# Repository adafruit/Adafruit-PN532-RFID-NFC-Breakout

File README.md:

## Adafruit NFC/RFID controller breakout board - v1.6 PCB

<a href="http://www.adafruit.com/products/364"><br/>
Click here to purchase one from the Adafruit shop</a>

PCB files for the Adafruit NFC/RFID controller breakout board - v1.6. Format is EagleCAD schematic and board layout
* https://www.adafruit.com/product/364

### Description

The PN532 is the most popular NFC chip, and is what is embedded in pretty much every phone or device that does NFC. It can pretty much do it all, such as read and write to tags and cards, communicate with phones (say for payment processing), and 'act' like a NFC tag. If you want to do any sort of embedded NFC work, this is the chip you'll want to use!

NFC (Near Field Communications) is a way for two devices very close to each other to communicate. Sort of like a very short range bluetooth that doesn't require authentication. It is an extension of RFID, so anything you can do with RFID you can do with NFC. You can do more stuff with NFC as well, such as communicate bi-directionally with cell phones

Because it can read and write tags, you can always just use this for RFID-tag projects. We carry a few different tags that work great with this chip. It can also work with any other NFC/RFID Type 1 thru 4 tag.

The PN532 is also very flexible, you can use 3.3V TTL UART at any baud rate, I2C or SPI to communicate with it. This chip is also strongly supported by [libnfc](http://www.libnfc.org/), simply plug in an FTDI cable and use the FTDI serial port device to communicate - this lets you do NFC dev using any Linux/Mac/Windows computer! We also include onboard power LED, 3.3V regulator and an FTDI header so you can plug in an [FTDI friend](http://www.adafruit.com/products/284) or [FTDI cable](http://www.adafruit.com/products/70) and use with libnfc.

Comes with: the PN532 breakout board including a tuned 13.56MHz stripline antenna, 0.1" header, 2 jumpers/shunts and a 4050 level shifter chip. We also toss in a  13.56MHz 1K card! ([You can get more tags from us here](http://www.adafruit.com/category/55))

### License

Adafruit invests time and resources providing this open source design, please support Adafruit and open-source hardware by purchasing products from [Adafruit](https://www.adafruit.com)!

Designed by Limor Fried/Ladyada for Adafruit Industries.

Creative Commons Attribution/Share-Alike, all text above must be included in any redistribution. See license.txt for additional details.

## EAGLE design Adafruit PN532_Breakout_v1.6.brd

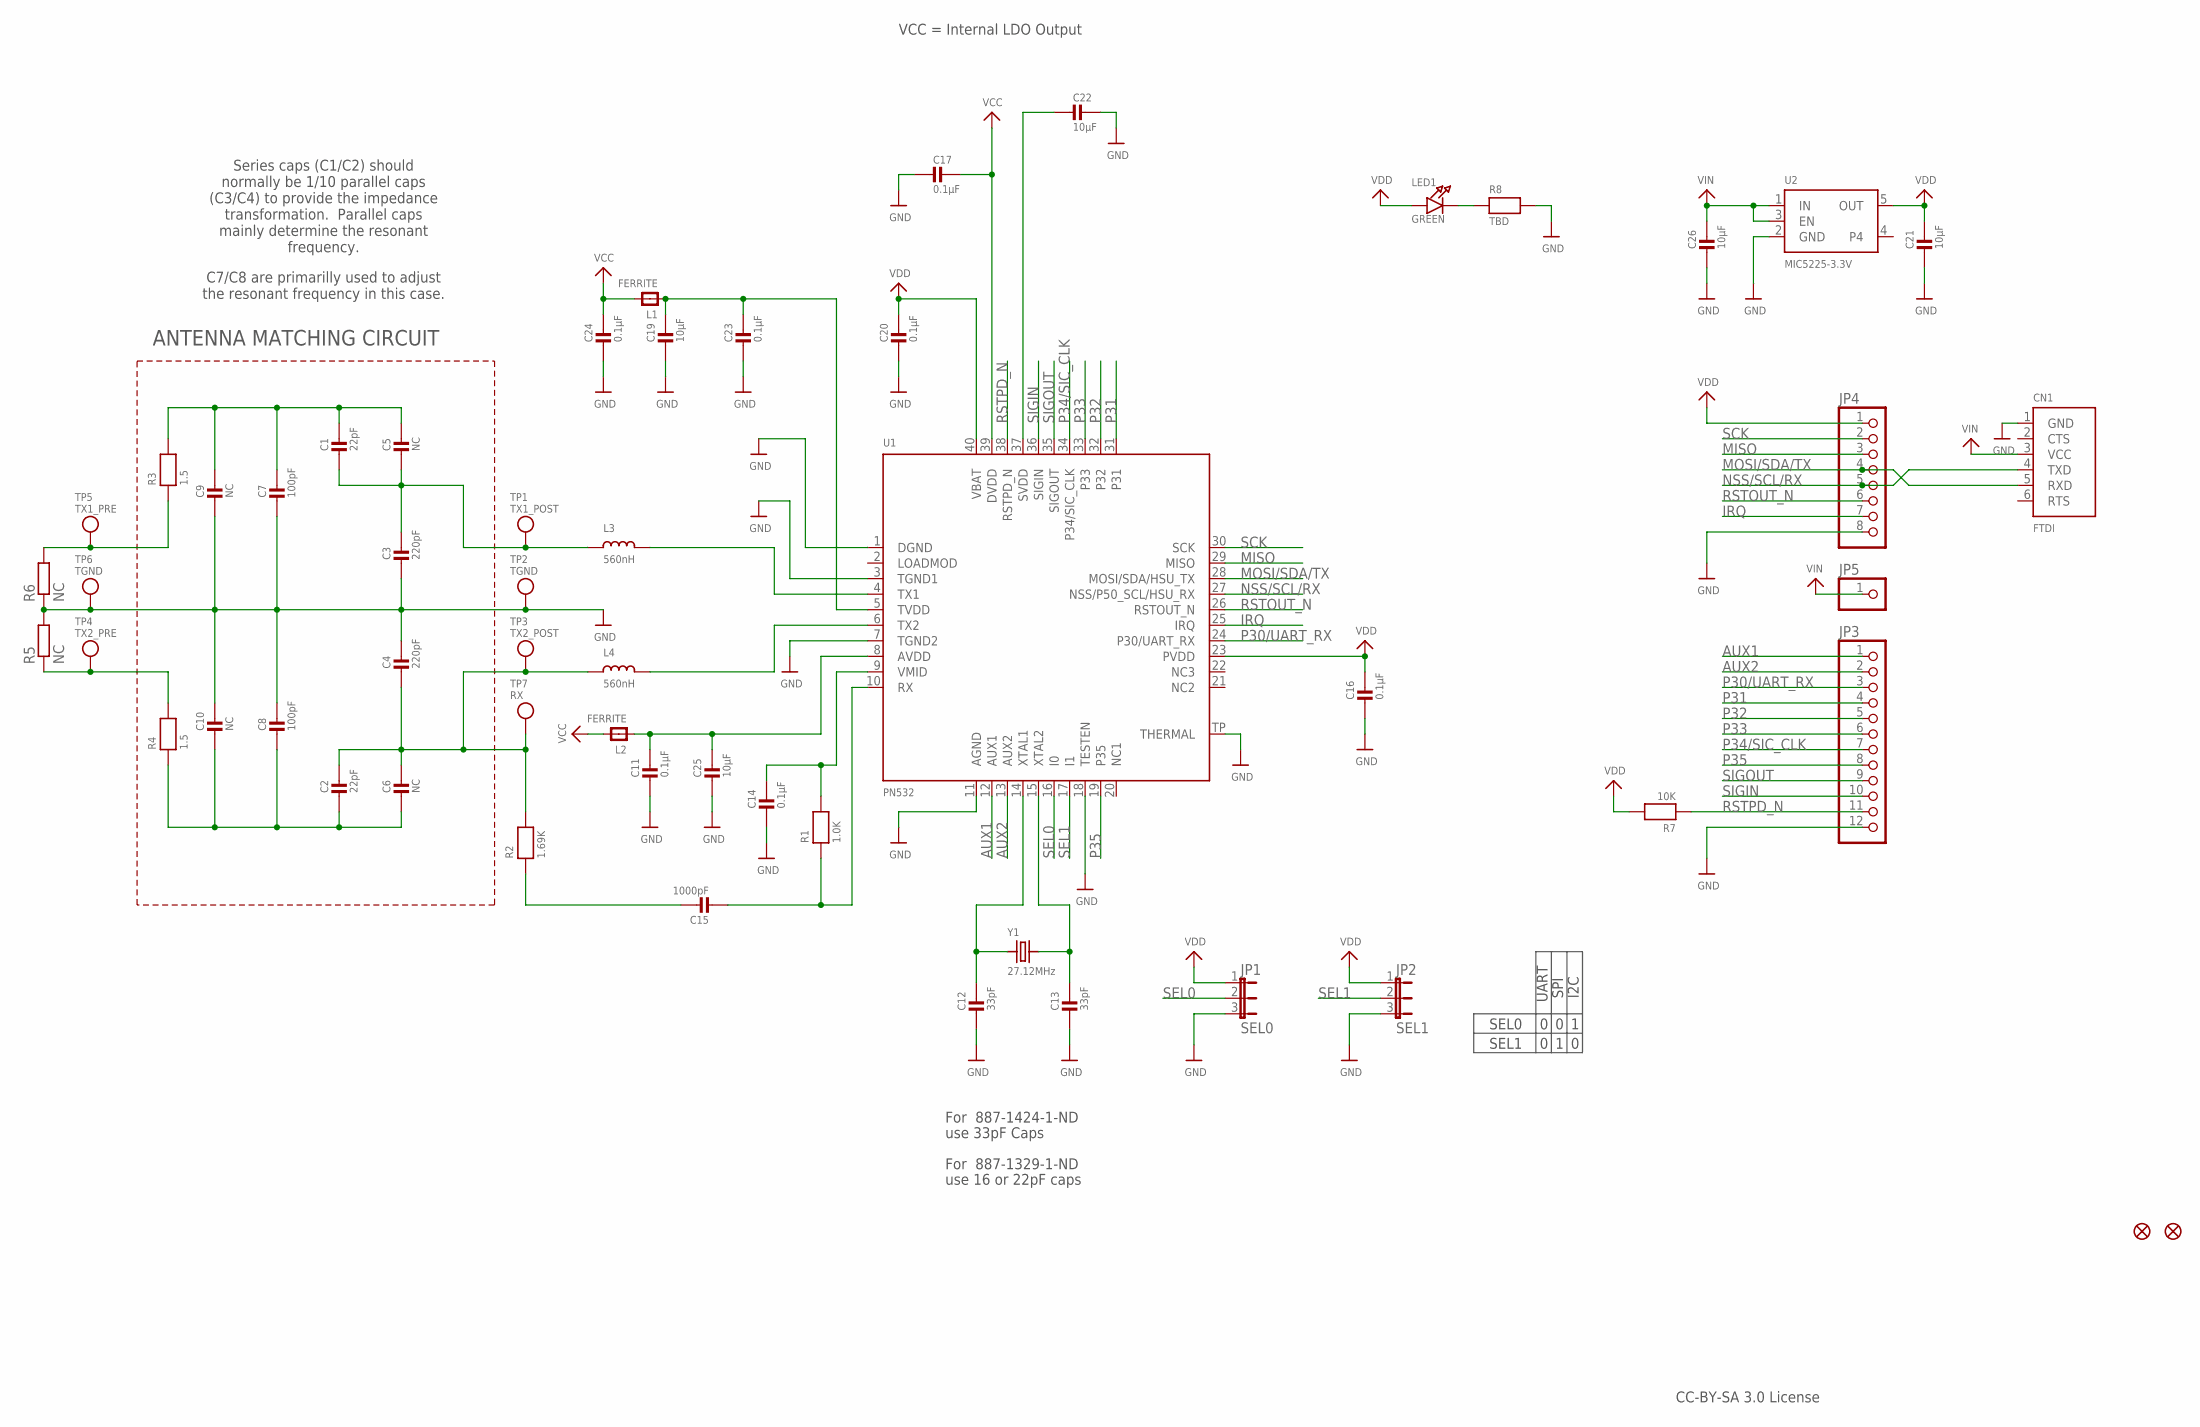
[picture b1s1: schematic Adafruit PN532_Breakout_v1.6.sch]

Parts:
C1, C2: 22pF; 0805-NO
C3, C4: 220pF; 0805-NO
C5, C6, C9, C10: NC; 0805-NO
C7, C8: 100pF; 0805-NO
C11, C14, C16, C17, C20, C23, C24: 0.1µF; 0805-NO
C12, C13: 33pF; 0805-NO
C15: 1000pF; 0805-NO
C19, C21, C22, C25, C26: 10µF; 0805-NO
CN1: FTDI; 1X06_ROUND
FID1, FID2: FIDUCIAL1X2.5; FIDUCIAL-1X2.5
JP1: SEL0; JUMPER3
JP2: SEL1; JUMPER3
JP3: HEADER-1X12; 1X12_ROUND
JP4: HEADER-1X8ROUND; 1X08_ROUND
JP5: HEADER-1X1ROUND; 1X01_ROUND
L1, L2: FERRITE; 0805
L3, L4: 560nH; 0805
LED1: GREEN; CHIPLED_0805_NOOUTLINE
R1: 1.0K; 0805-NO
R2: 1.69K; 0805-NO
R3, R4: 1.5; 0805-NO
R5, R6: NC; R0201
R7: 10K; 0805-NO
R8: TBD; 0805-NO
TP1: TX1_POST; TESTPOINT_ROUND_1MM
TP2, TP6: TGND; TESTPOINT_ROUND_1MM
TP3: TX2_POST; TESTPOINT_ROUND_1MM
TP4: TX2_PRE; TESTPOINT_ROUND_1MM
TP5: TX1_PRE; TESTPOINT_ROUND_1MM
TP7: RX; TESTPOINT_ROUND_1MM
U1: PN532; HVQFN40-6X6
U2: MIC5225-3.3V; SOT23-5
Y1: 27.12MHz; CRYSTAL_3.2X2.5

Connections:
+5.0V: C26.1, CN1.3 (VCC), JP5.1, U2.1 (IN), U2.3 (EN)
AUX1: JP3.1, U1.12 (AUX1)
AUX2: JP3.2, U1.13 (AUX2)
GND: C3.2, C4.1, C7.2, C8.1, C9.2, C10.1, C11.2, C12.2, C13.2, C14.2, C16.2, C17.2, C19.2, C20.2, C21.2, C22.1, C23.2, C24.2, C25.2, C26.2, CN1.1 (GND), JP1.3, JP2.3, JP3.12, JP4.8, R5.2, R6.1, R8.2, TP2.P$1, TP6.P$1, U1.1 (DGND), U1.3 (TGND1), U1.7 (TGND2), U1.11 (AGND), U1.18 (TESTEN), U1.TP (THERMAL), U2.2 (GND)
IRQ: JP4.7, U1.25 (IRQ)
MISO: JP4.3, U1.29 (MISO)
MOSI/SDA/TX: CN1.5 (RXD), JP4.4, U1.28 (MOSI/SDA/HSU_TX)
unnamed: L3.2, U1.4 (TX1)
unnamed: L4.2, U1.6 (TX2)
unnamed: C1.2, C3.1, C5.2, L3.1, TP1.P$1
unnamed: R3.1, R6.2, TP5.P$1
unnamed: R4.2, R5.1, TP4.P$1
unnamed: LED1.C, R8.1
unnamed: C12.1, U1.14 (XTAL1), Y1.1
unnamed: C13.1, U1.15 (XTAL2), Y1.2
unnamed: C15.1, R2.1
unnamed: C14.1, R1.2, U1.9 (VMID)
unnamed: C15.2, R1.1, U1.10 (RX)
unnamed: C2.1, C4.2, C6.1, L4.1, R2.2, TP3.P$1, TP7.P$1
unnamed: C11.1, C25.1, L2.1, U1.8 (AVDD)
unnamed: C19.1, C23.1, L1.1, U1.5 (TVDD)
unnamed: C22.2, U1.37 (SVDD)
NSS/SCL/RX: CN1.4 (TXD), JP4.5, U1.27 (NSS/P50_SCL/HSU_RX)
P30/UART_RX: JP3.3, U1.24 (P30/UART_RX)
P31: JP3.4, U1.31
P32: JP3.5, U1.32
P33: JP3.6, U1.33
P34/SIC_CLK: JP3.7, U1.34 (P34/SIC_CLK)
P35: JP3.8, U1.19 (P35)
RSTOUT_N: JP4.6, U1.26 (RSTOUT_N)
RSTPD_N: JP3.11, R7.1, U1.38 (RSTPD_N)
SCK: JP4.2, U1.30 (SCK)
SEL0: JP1.2, U1.16 (I0)
SEL1: JP2.2, U1.17 (I1)
SIGIN: JP3.10, U1.36 (SIGIN)
SIGOUT: JP3.9, U1.35 (SIGOUT)
TX1_ANTENNA: C1.1, C5.1, C7.1, C9.1, R3.2
TX2_ANTENNA: C2.2, C6.2, C8.2, C10.2, R4.1
VCC: C17.1, C24.1, L1.2, L2.2, U1.39 (DVDD)
VDD: C16.1, C20.1, C21.1, JP1.1, JP2.1, JP4.1, LED1.A, R7.2, U1.23 (PVDD), U1.40 (VBAT), U2.5 (OUT)

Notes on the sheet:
ANTENNA MATCHING CIRCUIT
SEL0
SEL1
UART
SPI
I2C
CC-BY-SA 3.0 License
For 887-1329-1-ND
use 16 or 22pF caps
For 887-1424-1-ND
use 33pF Caps
VCC = Internal LDO Output
Series caps (C1/C2) should normally be 1/10 parallel caps (C3/C4) to provide the impedance transformation. Parallel caps mainly determine the resonant frequency.
C7/C8 are primarilly used to adjust the resonant frequency in this case.

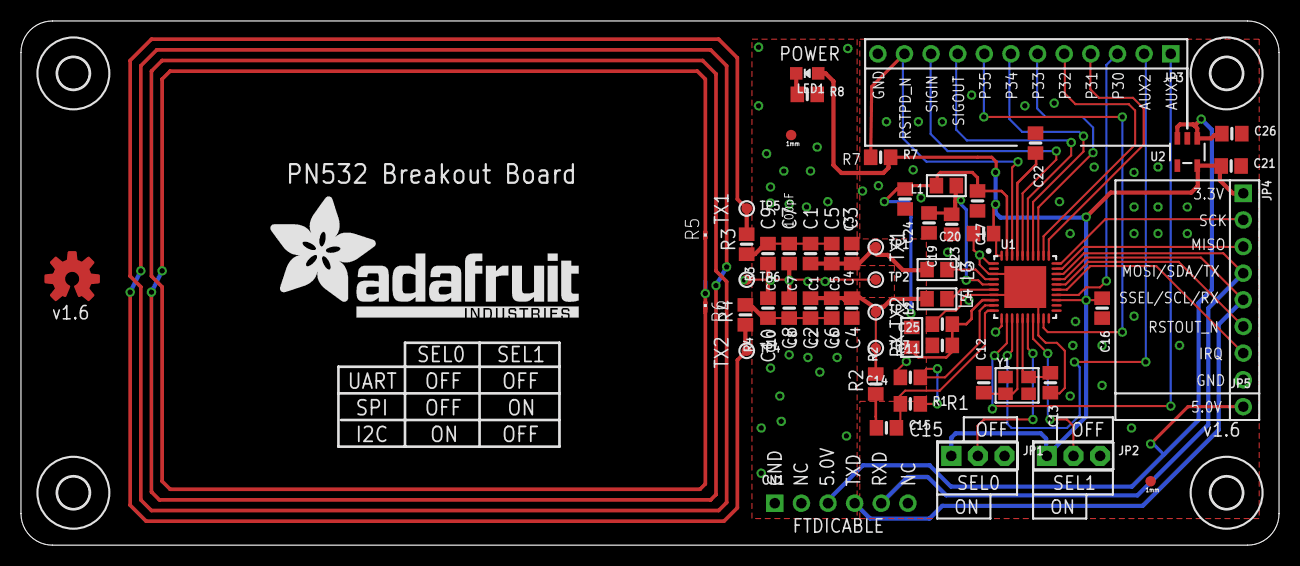
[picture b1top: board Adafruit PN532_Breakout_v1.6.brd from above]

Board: 2 copper layers, 120.0 x 50.0 mm, 62 parts (0 on the bottom side), 40 nets.

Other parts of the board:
U$1: ADAFRUIT_TEXT_30MM
U$6, U$36, U$37, U$38: MOUNTINGHOLE_3.0
U$50: OSHWLOGO_TOP_0.2

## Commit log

2012-07-09 init
2012-07-09 readme
2018-11-16 v1.6
2019-07-16 updated to use cookiecutter for pcb repos
